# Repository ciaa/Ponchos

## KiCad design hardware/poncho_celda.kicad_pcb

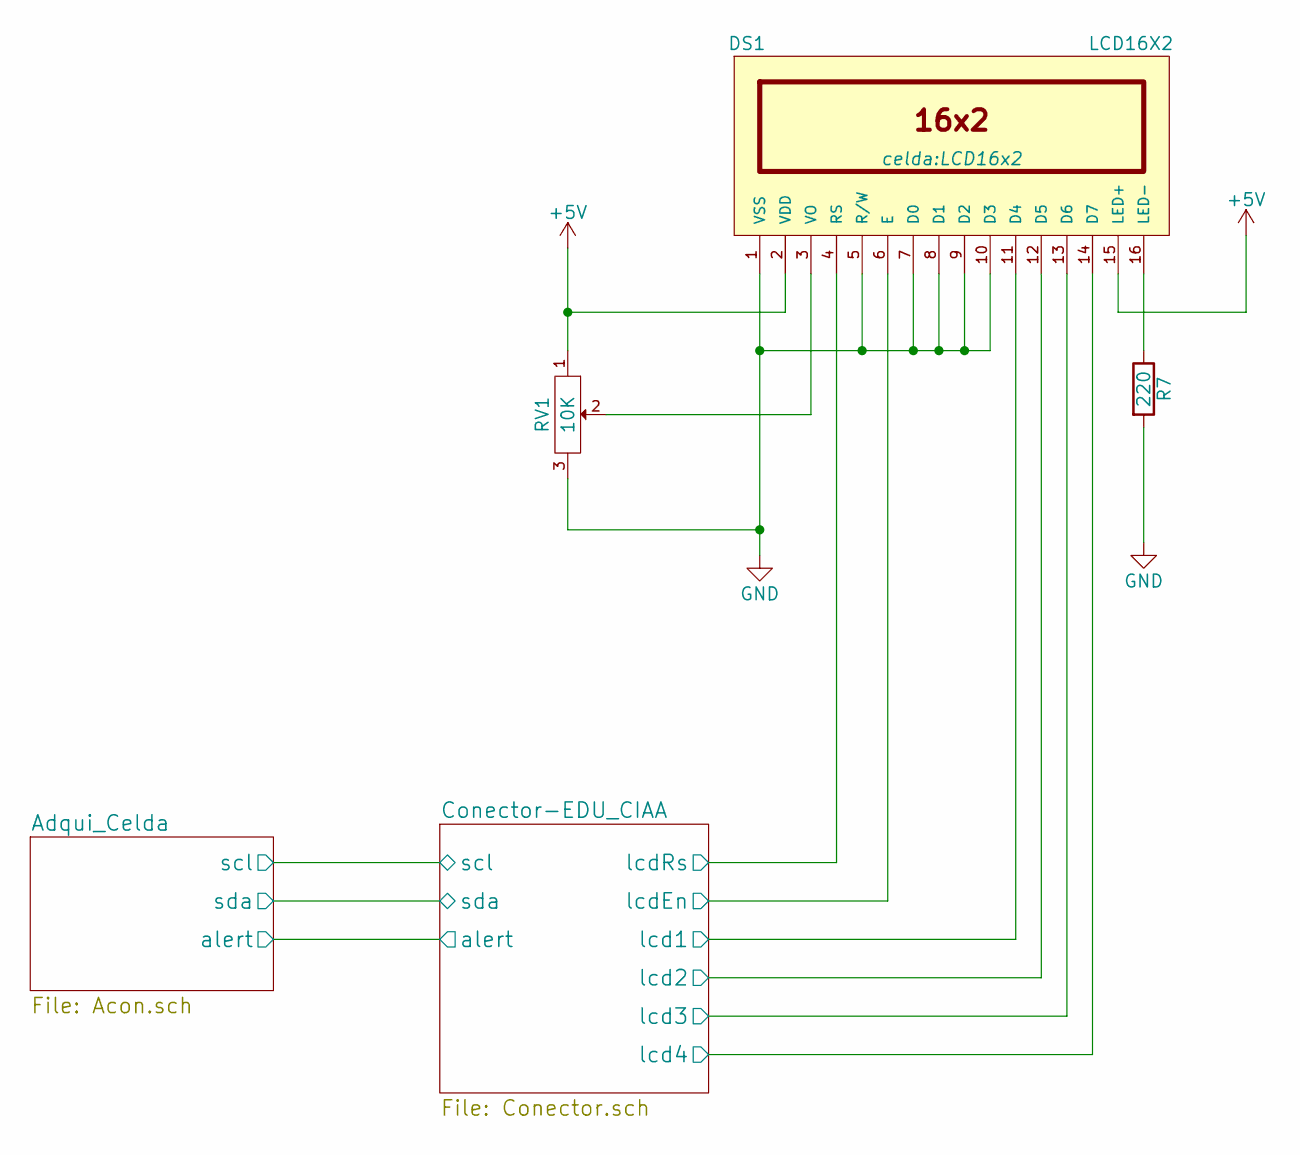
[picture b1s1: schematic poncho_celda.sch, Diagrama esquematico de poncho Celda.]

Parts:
DS1: LCD16X2; LCD16x2
R7: 220; R_1206_HandSoldering
RV1: 10K; POT_SMD

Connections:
+5V: DS1.2 (VDD), DS1.15 (LED+), RV1.1; also elsewhere on the board
/Conector-EDU_CIAA/lcd1: DS1.11 (D4); also elsewhere on the board
/Conector-EDU_CIAA/lcd2: DS1.12 (D5); also elsewhere on the board
/Conector-EDU_CIAA/lcd3: DS1.13 (D6); also elsewhere on the board
/Conector-EDU_CIAA/lcd4: DS1.14 (D7); also elsewhere on the board
/Conector-EDU_CIAA/lcdEn: DS1.6 (E); also elsewhere on the board
/Conector-EDU_CIAA/lcdRs: DS1.4 (RS); also elsewhere on the board
GND: DS1.1 (VSS), DS1.5 (R/W), DS1.7 (D0), DS1.8 (D1), DS1.9 (D2), DS1.10 (D3), R7.2, RV1.3; also elsewhere on the board
unnamed: DS1.3 (VO), RV1.2
unnamed: DS1.16 (LED-), R7.1

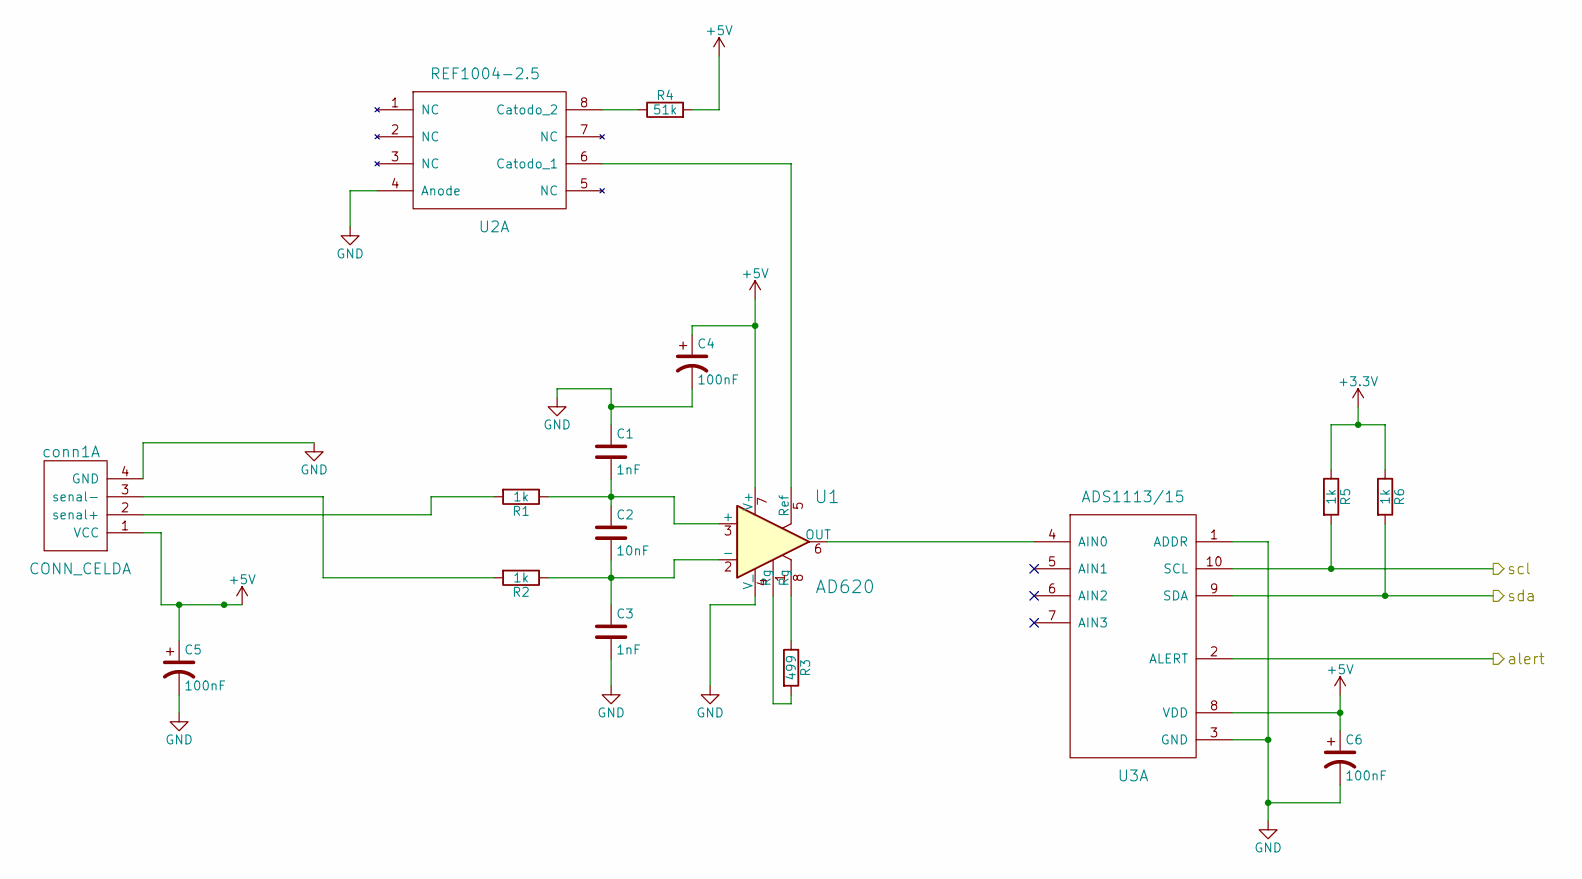
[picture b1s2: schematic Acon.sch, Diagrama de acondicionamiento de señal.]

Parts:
C1, C3: 1nF; C_0603_HandSoldering
C2: 10nF; C_0603_HandSoldering
C4, C5, C6: 100nF; C_0805_HandSoldering
R1, R2, R5, R6: 1k; R_1206_HandSoldering
R3: 499; R_1206_HandSoldering
R4: 51k; R_1206_HandSoldering
U1: AD620; SOIC-8
U2: REF1004-2.5; SOIC-8
U3: ADS1113/15; TSSOP-10_3x3mm_Pitch0.5mm
conn1: CONN_CELDA; bornier4

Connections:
+3V3: R5.1, R6.1; also elsewhere on the board
+5V: C4.1, C5.1, C6.1, R4.2, U1.7 (V+), U3.8 (VDD), conn1.1 (VCC); also elsewhere on the board
/Adqui_Celda/alert: U3.2 (ALERT); also elsewhere on the board
/Adqui_Celda/scl: R5.2, U3.10 (SCL); also elsewhere on the board
/Adqui_Celda/sda: R6.2, U3.9 (SDA); also elsewhere on the board
GND: C1.1, C3.2, C4.2, C5.2, C6.2, U1.4 (V_), U2.4 (Anode), U3.1 (ADDR), U3.3 (GND), conn1.4 (GND); also elsewhere on the board
unnamed: C1.2, C2.1, R1.1, U1.3 (+)
unnamed: C2.2, C3.1, R2.1, U1.2 (-)
unnamed: R1.2, conn1.2 (senal+)
unnamed: R2.2, conn1.3 (senal-)
unnamed: R3.1, U1.8 (Rg)
unnamed: R3.2, U1.1 (Rg)
unnamed: R4.1, U2.8 (Catodo_2)
unnamed: U1.5 (Ref), U2.6 (Catodo_1)
unnamed: U1.6 (OUT), U3.4 (AIN0)

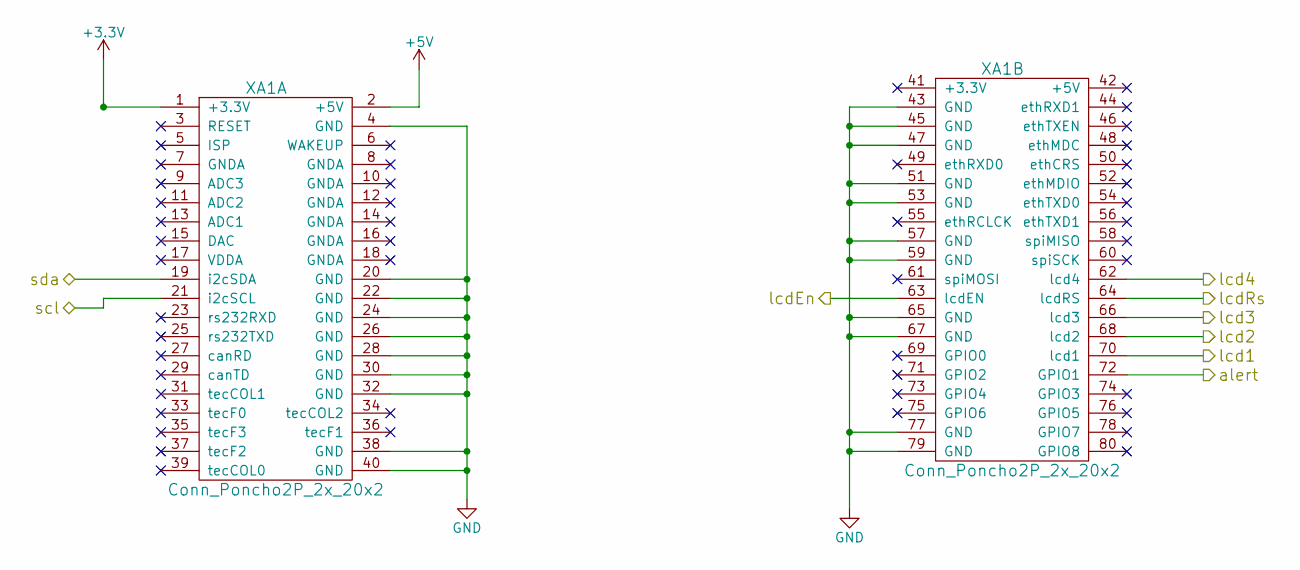
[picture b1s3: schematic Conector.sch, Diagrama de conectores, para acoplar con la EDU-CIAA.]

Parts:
XA1: Conn_Poncho2P_2x_20x2; Conn_Poncho_SinBorde

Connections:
+3V3: XA1.1 (+3.3V); also elsewhere on the board
+5V: XA1.2 (+5V); also elsewhere on the board
/Adqui_Celda/alert: XA1.72 (GPIO1); also elsewhere on the board
/Adqui_Celda/scl: XA1.21 (i2cSCL); also elsewhere on the board
/Adqui_Celda/sda: XA1.19 (i2cSDA); also elsewhere on the board
/Conector-EDU_CIAA/lcd1: XA1.70 (lcd1); also elsewhere on the board
/Conector-EDU_CIAA/lcd2: XA1.68 (lcd2); also elsewhere on the board
/Conector-EDU_CIAA/lcd3: XA1.66 (lcd3); also elsewhere on the board
/Conector-EDU_CIAA/lcd4: XA1.62 (lcd4); also elsewhere on the board
/Conector-EDU_CIAA/lcdEn: XA1.63 (lcdEN); also elsewhere on the board
/Conector-EDU_CIAA/lcdRs: XA1.64 (lcdRS); also elsewhere on the board
GND: XA1.4 (GND), XA1.20 (GND), XA1.22 (GND), XA1.24 (GND), XA1.26 (GND), XA1.28 (GND), XA1.30 (GND), XA1.32 (GND), XA1.38 (GND), XA1.40 (GND), XA1.43 (GND), XA1.45 (GND), XA1.47 (GND), XA1.51 (GND), XA1.53 (GND), XA1.57 (GND), XA1.59 (GND), XA1.65 (GND), XA1.67 (GND), XA1.77 (GND), XA1.79 (GND); also elsewhere on the board

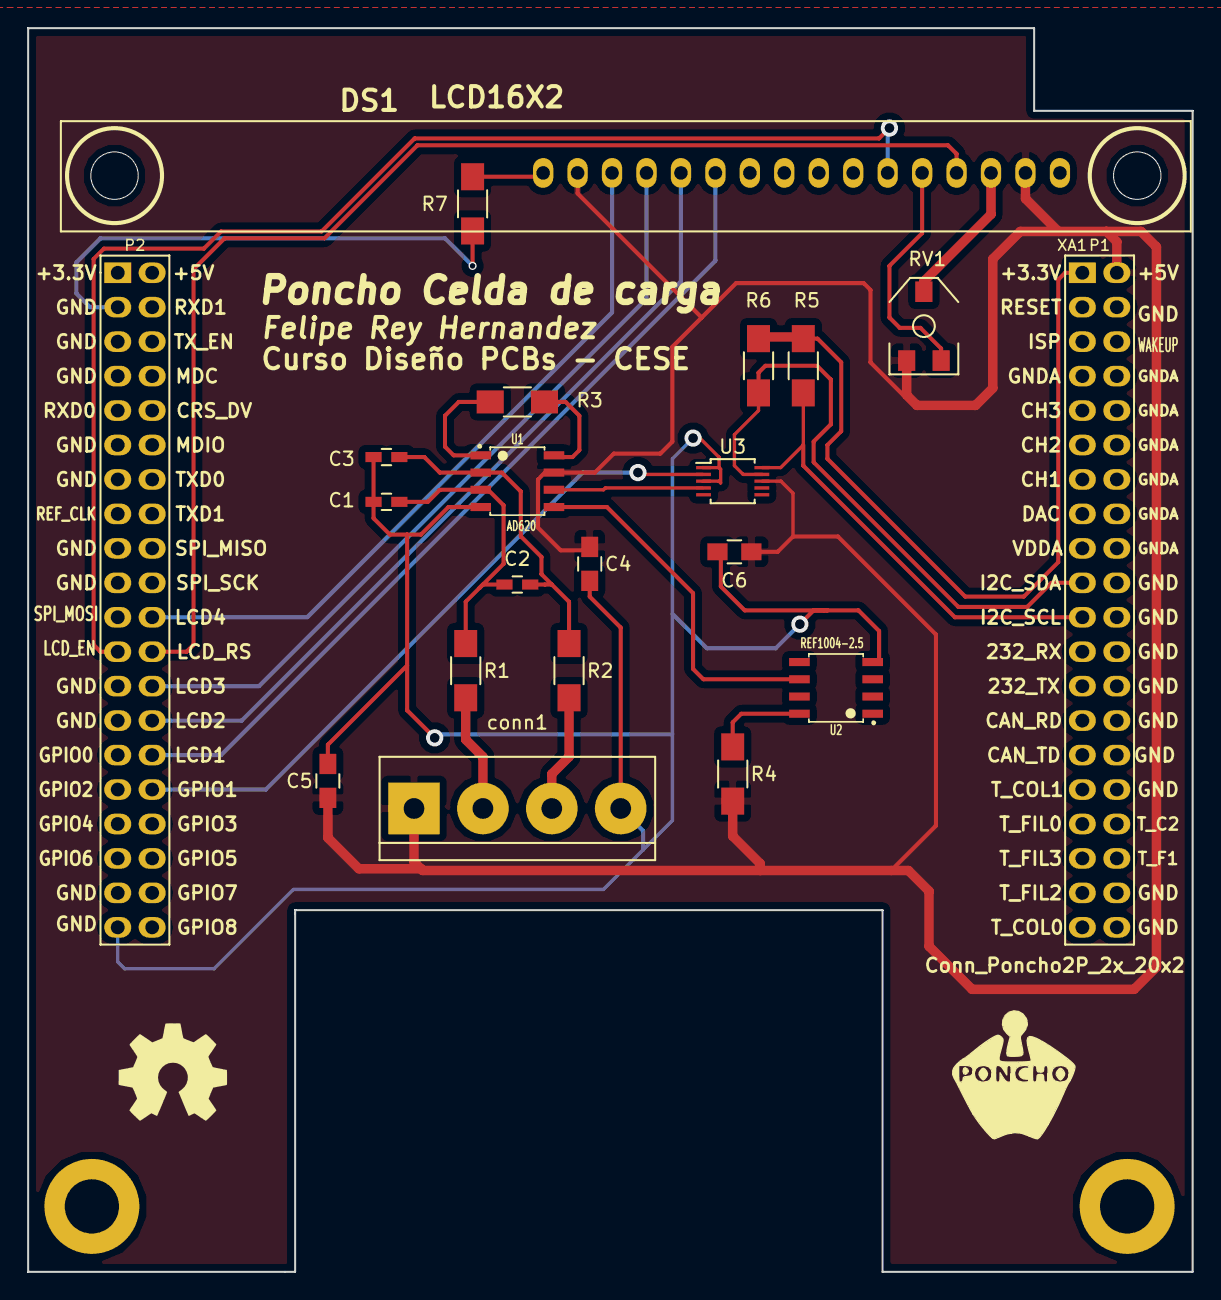
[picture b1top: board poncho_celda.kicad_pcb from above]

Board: 2 copper layers, 85.9 x 91.7 mm, 21 parts (0 on the bottom side), 23 nets.

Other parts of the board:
G101: Logo_OSHWA

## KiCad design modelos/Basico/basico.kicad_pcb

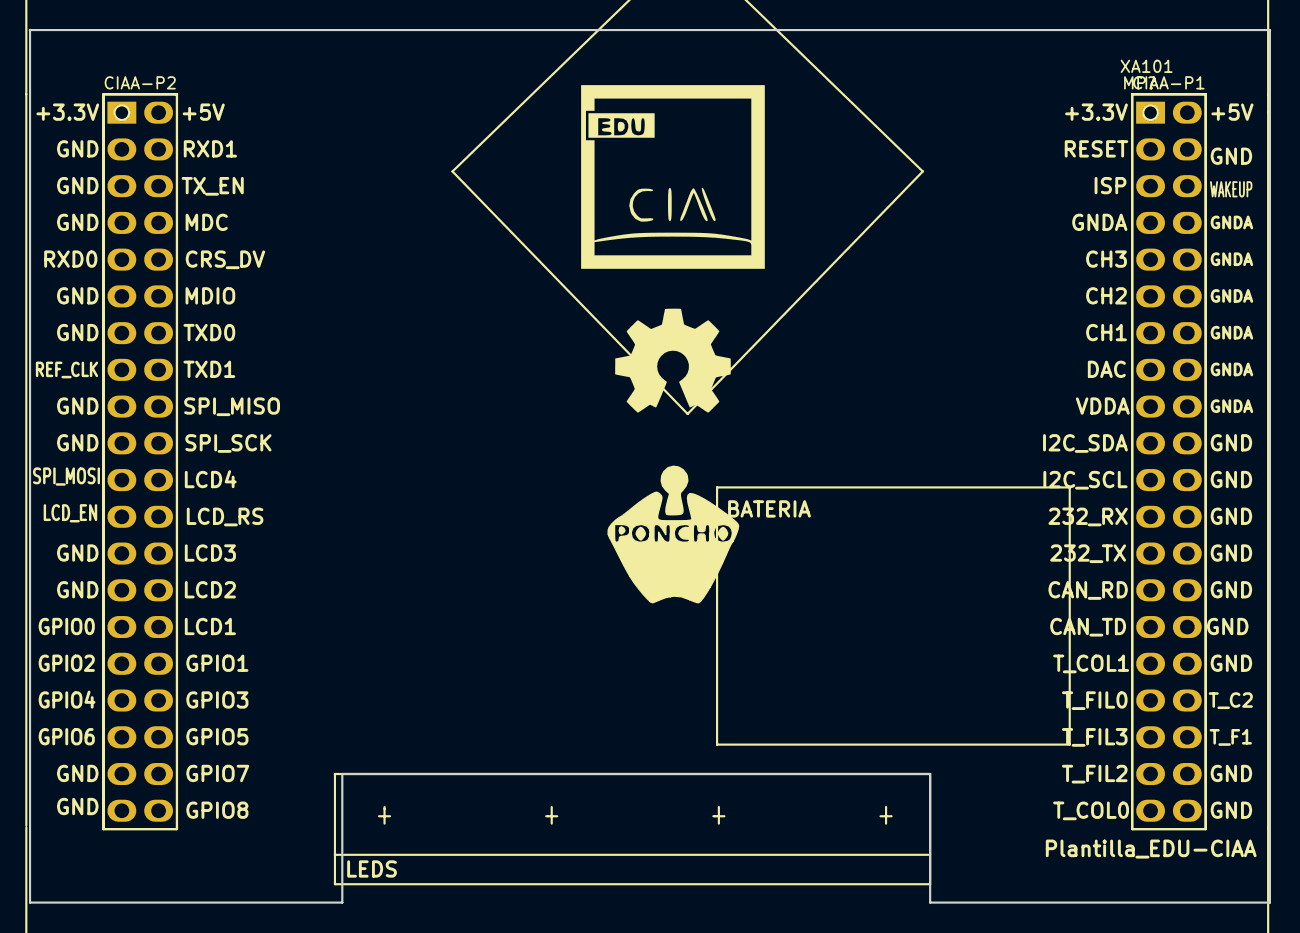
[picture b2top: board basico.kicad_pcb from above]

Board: 2 copper layers, 85.7 x 60.3 mm, 3 parts (0 on the bottom side), 4 nets, no tracks yet.

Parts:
G101: Logo_OSHWA
MP?: Plantilla_EDU-CIAA
XA101: Conn_Poncho2P_2x_20x2; Conn_Poncho_SinBorde

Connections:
+3.3VP: XA101.1, XA101.41
+5V: XA101.2, XA101.42
GND: XA101.4, XA101.20, XA101.22, XA101.24, XA101.26, XA101.28, XA101.30, XA101.32, XA101.38, XA101.40, XA101.43, XA101.45, XA101.47, XA101.51, XA101.53, XA101.57, XA101.59, XA101.65, XA101.67, XA101.77, XA101.79
GNDA: XA101.7, XA101.8, XA101.10, XA101.12, XA101.14, XA101.16, XA101.18

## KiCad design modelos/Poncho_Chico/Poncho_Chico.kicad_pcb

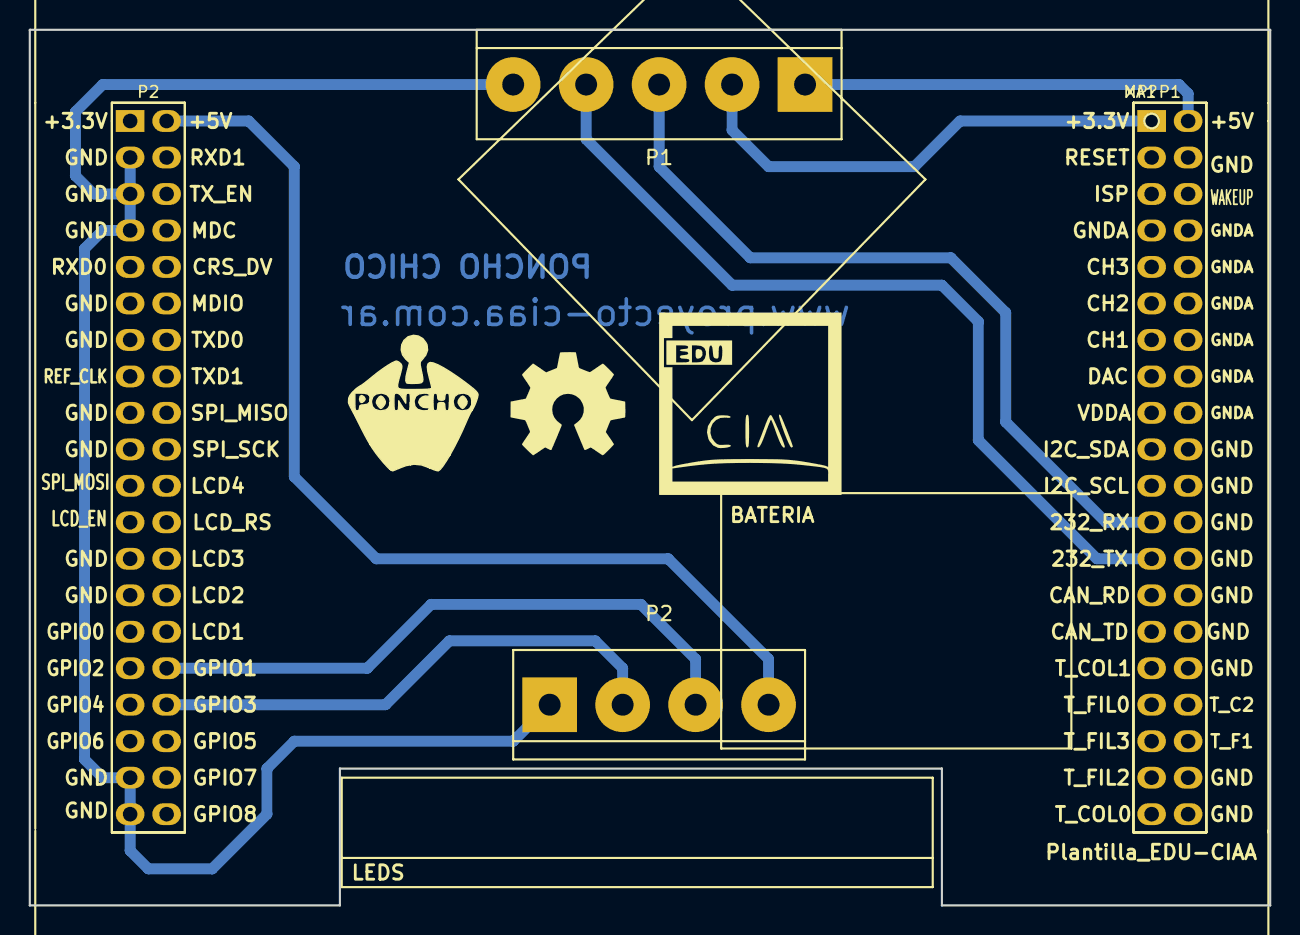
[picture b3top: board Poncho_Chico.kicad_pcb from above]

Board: 2 copper layers, 86.4 x 61.0 mm, 5 parts (0 on the bottom side), 8 nets.

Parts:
G101: Logo_OSHWA
MP?: Plantilla_EDU-CIAA
P1: CONN_5; bornier5
P2: CONN_4; bornier4
XA1: Conn_PonchoMP_2x_20x2; Conn_Poncho_Chico

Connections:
+3.3V: P1.2, XA1.1
+5V: P1.1, XA1.2
+5VP: P2.4, XA1.42
GND: P1.5, P2.1, XA1.43, XA1.45, XA1.47, XA1.77, XA1.79
unnamed: P1.3, XA1.23
unnamed: P1.4, XA1.25
unnamed: P2.2, XA1.74
unnamed: P2.3, XA1.72

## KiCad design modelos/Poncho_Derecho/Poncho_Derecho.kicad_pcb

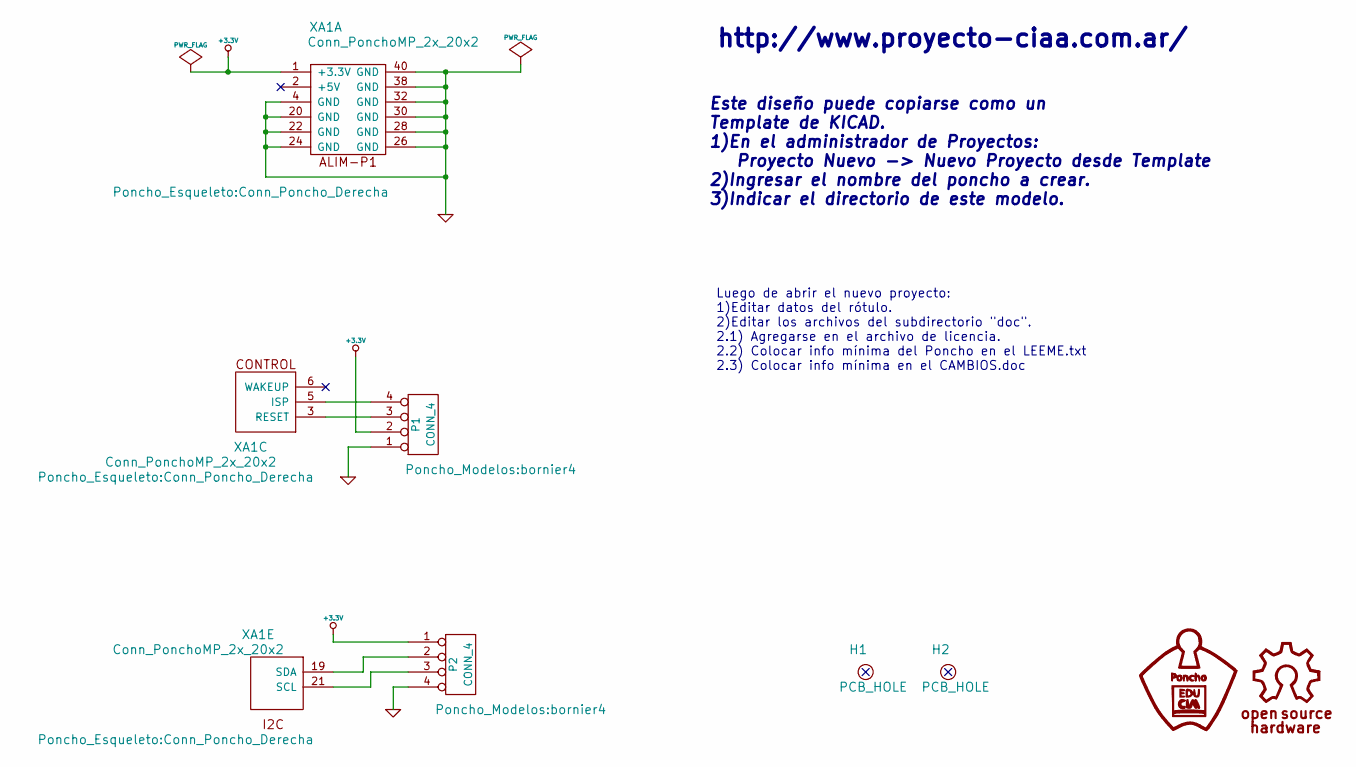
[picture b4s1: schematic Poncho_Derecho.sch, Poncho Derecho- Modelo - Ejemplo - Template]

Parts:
H1, H2: PCB_HOLE; Led_Hole
P1, P2: CONN_4; bornier4
XA1: Conn_PonchoMP_2x_20x2; Conn_Poncho_Derecha

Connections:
+3.3V: P1.2, P2.1, XA1.1 (+3.3V)
GND: P1.1, P2.4, XA1.4 (GND), XA1.20 (GND), XA1.22 (GND), XA1.24 (GND), XA1.26 (GND), XA1.28 (GND), XA1.30 (GND), XA1.32 (GND), XA1.38 (GND), XA1.40 (GND)
unnamed: P1.3, XA1.3 (RESET)
unnamed: P1.4, XA1.5 (ISP)
unnamed: P2.2, XA1.19 (SDA)
unnamed: P2.3, XA1.21 (SCL)

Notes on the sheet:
Este diseño puede copiarse como un Template de KICAD. 1)En el administrador de Proyectos: Proyecto Nuevo -> Nuevo Proyecto desde Template 2)Ingresar el nombre del poncho a crear. 3)Indicar el directorio de este modelo.
http://www.proyecto-ciaa.com.ar/
Luego de abrir el nuevo proyecto: 1)Editar datos del rótulo. 2)Editar los archivos del subdirectorio "doc". 2.1) Agregarse en el archivo de licencia. 2.2) Colocar info mínima del Poncho en el LEEME.txt 2.3) Colocar info mínima en el CAMBIOS.doc

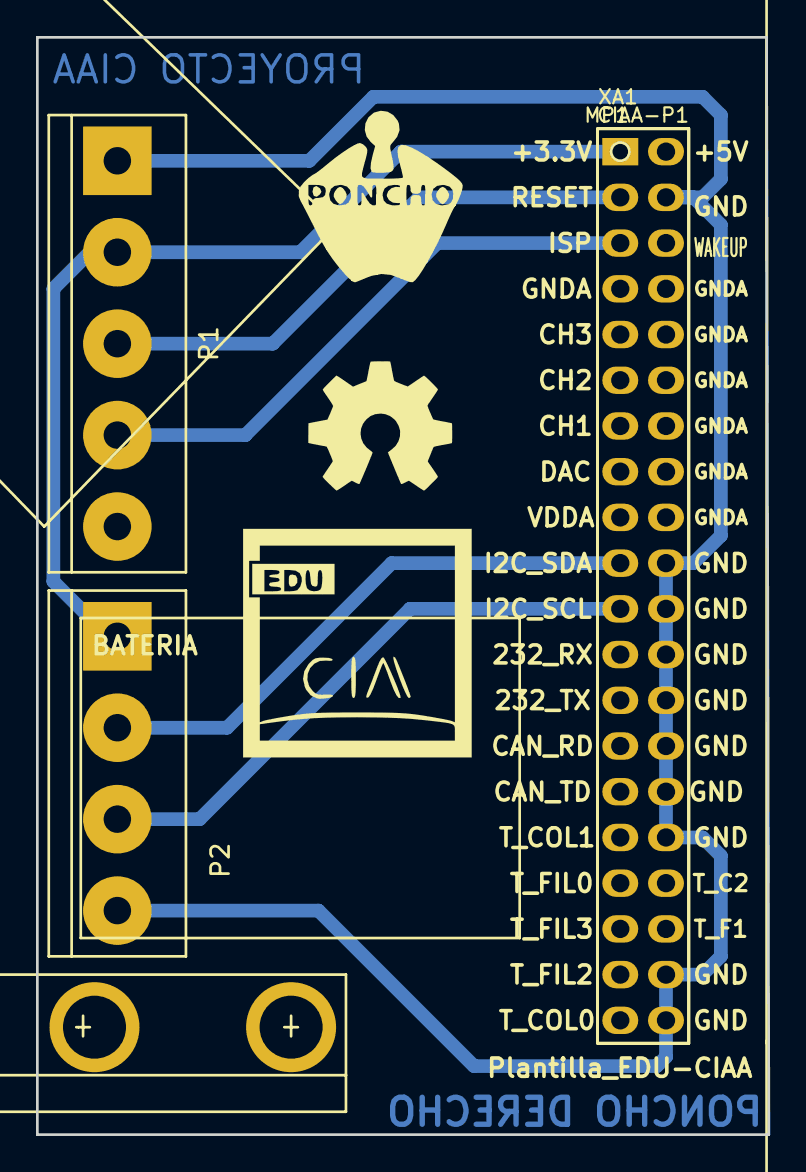
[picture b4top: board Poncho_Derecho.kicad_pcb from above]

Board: 2 copper layers, 40.6 x 61.0 mm, 7 parts (0 on the bottom side), 6 nets.

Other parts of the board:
G101: Logo_OSHWA
MP1: Plantilla_EDU-CIAA

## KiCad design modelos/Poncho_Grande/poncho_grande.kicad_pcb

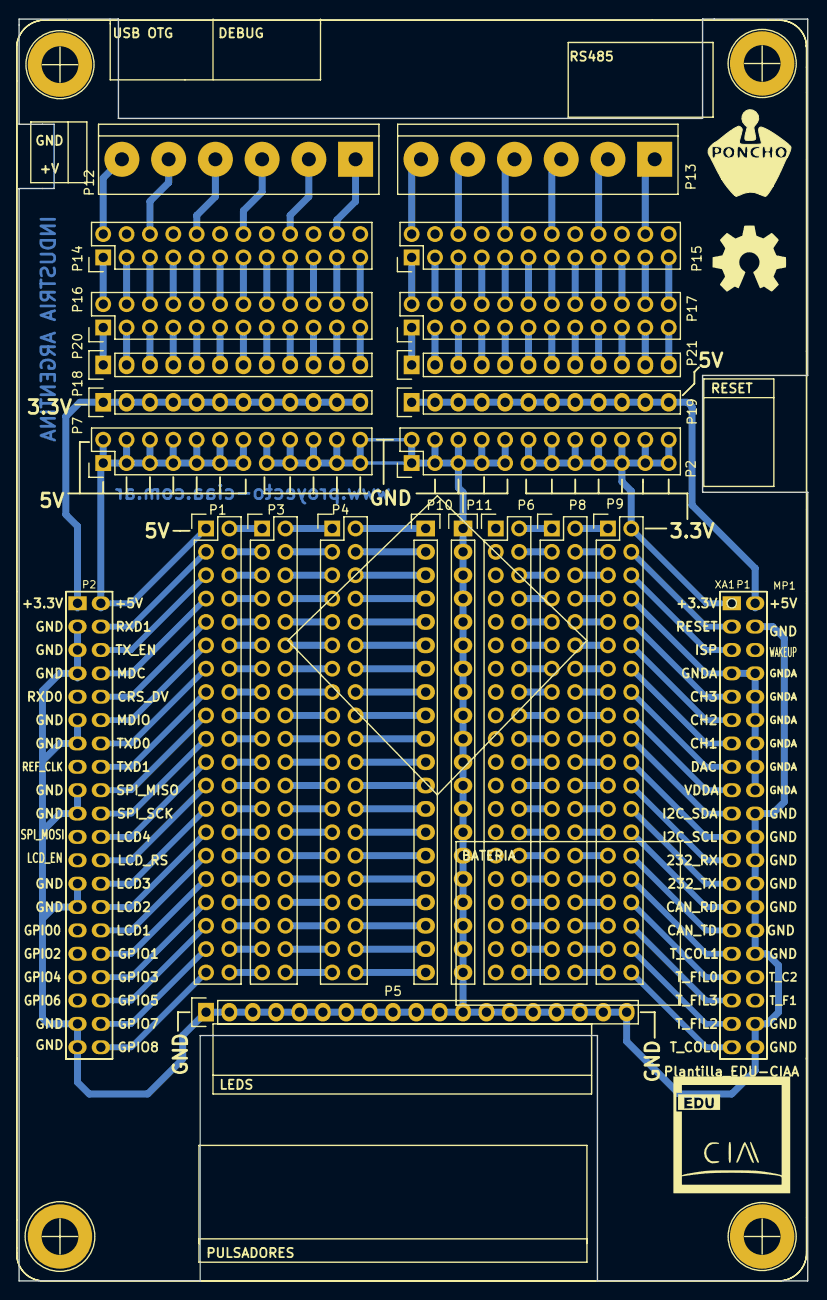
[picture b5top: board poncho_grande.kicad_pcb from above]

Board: 2 copper layers, 85.7 x 137.2 mm, 24 parts (0 on the bottom side), 203 nets.

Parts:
G101: Logo_OSHWA
MP1: Plantilla_EDU-CIAA
P1, P3, P4, P6, P8, P9: CONN_02X20; Pin_Header_Straight_2x20
P2, P7: CONN_01X20; Pin_Header_Straight_2x12
P5: CONN_01X19; Pin_Header_Straight_1x19
P10, P11: CONN_01X20; Pin_Header_Straight_1x20
P12, P13: CONN_01X06; bornier6
P14, P15, P16, P17: CONN_02X12; Pin_Header_Straight_2x12
P18, P19, P20, P21: CONN_01X12; Pin_Header_Straight_1x12
XA1: poncho_grande

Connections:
+3.3V: P2.11, P2.12, P2.13, P2.14, P2.15, P2.16, P2.17, P2.18, P2.19, P2.20, P2.21, P2.22, P2.23, P2.24, P9.2, XA1.1
+3.3VADC: P9.18, XA1.17
+3.3VP: P18.1, P18.2, P18.3, P18.4, P18.5, P18.6, P18.7, P18.8, P18.9, P18.10, P18.11, P18.12, XA1.41
+5V: P19.1, P19.2, P19.3, P19.4, P19.5, P19.6, P19.7, P19.8, P19.9, P19.10, P19.11, P19.12, XA1.2
+5VP: P1.1, P7.1, P7.2, P7.3, P7.4, P7.5, P7.6, P7.7, P7.8, P7.9, P7.10, P7.11, P7.12, P7.13, P7.14, XA1.42
/Circuito Principal/ADC1: P9.14, XA1.13
/Circuito Principal/ADC2: P9.12, XA1.11
/Circuito Principal/ADC3: P9.10, XA1.9
/Circuito Principal/COL0: P9.40, XA1.39
/Circuito Principal/COL1: P9.32, XA1.31
/Circuito Principal/CRS: P1.9, XA1.50
/Circuito Principal/DAC: P9.16, XA1.15
/Circuito Principal/F0: P9.34, XA1.33
/Circuito Principal/F2: P9.38, XA1.37
/Circuito Principal/F3: P9.36, XA1.35
/Circuito Principal/GPIO1: P1.31, XA1.72
/Circuito Principal/GPIO3: P1.33, XA1.74
/Circuito Principal/GPIO5: P1.35, XA1.76
/Circuito Principal/GPIO7: P1.37, XA1.78
/Circuito Principal/GPIO8: P1.39, XA1.80
/Circuito Principal/ISP: P9.6, XA1.5
/Circuito Principal/LCD1: P1.29, XA1.70
/Circuito Principal/LCD2: P1.27, XA1.68
/Circuito Principal/LCD3: P1.25, XA1.66
/Circuito Principal/LCD4: P1.21, XA1.62
/Circuito Principal/MDC: P1.7, XA1.48
/Circuito Principal/MDIO: P1.11, XA1.52
/Circuito Principal/MISO: P1.17, XA1.58
/Circuito Principal/RD: P9.28, XA1.27
/Circuito Principal/RESET: P9.4, XA1.3
/Circuito Principal/RS: P1.23, XA1.64
/Circuito Principal/RXD: P9.24, XA1.23
/Circuito Principal/RXD1: P1.3, XA1.44
/Circuito Principal/SCL: P9.22, XA1.21
/Circuito Principal/SDA: P9.20, XA1.19
/Circuito Principal/TD: P9.30, XA1.29
/Circuito Principal/TXD: P9.26, XA1.25
/Circuito Principal/TXD0: P1.13, XA1.54
/Circuito Principal/TXD1: P1.15, XA1.56
/Circuito Principal/TXEN: P1.5, XA1.46
/Circuito Principal/spiCCK: P1.19, XA1.60
GND: P2.1, P2.2, P2.3, P2.4, P2.5, P2.6, P2.7, P2.8, P2.9, P2.10, P5.1, P5.2, P5.3, P5.4, P5.5, P5.6, P5.7, P5.8, P5.9, P5.10, P5.11, P5.12, P5.13, P5.14, P5.15, P5.16, P5.17, P5.18, P5.19, P7.15, P7.16, P7.17, P7.18, P7.19, P7.20, P7.21, P7.22, P7.23, P7.24, P11.1, P11.2, P11.3, P11.4, P11.5, P11.6, P11.7, P11.8, P11.9, P11.10, P11.11, P11.12, P11.13, P11.14, P11.15, P11.16, P11.17, P11.18, P11.19, P11.20, XA1.4, XA1.20, XA1.22, XA1.24, XA1.26, XA1.28, XA1.30, XA1.32, XA1.38, XA1.40, XA1.43, XA1.45, XA1.47, XA1.51, XA1.53, XA1.57, XA1.59, XA1.65, XA1.67, XA1.77, XA1.79
GNDA: P9.8, XA1.7, XA1.8, XA1.10, XA1.12, XA1.14, XA1.16, XA1.18
unnamed: P1.2, P3.1
unnamed: P1.4, P3.3
unnamed: P1.6, P3.5
unnamed: P1.8, P3.7
unnamed: P1.10, P3.9
unnamed: P1.12, P3.11
unnamed: P1.14, P3.13
unnamed: P1.16, P3.15
unnamed: P1.18, P3.17
unnamed: P1.20, P3.19
unnamed: P1.22, P3.21
unnamed: P1.24, P3.23
unnamed: P1.26, P3.25
unnamed: P1.28, P3.27
unnamed: P1.30, P3.29
unnamed: P1.32, P3.31
unnamed: P1.34, P3.33
unnamed: P1.36, P3.35
unnamed: P1.38, P3.37
unnamed: P1.40, P3.39
unnamed: P3.2, P4.1
unnamed: P3.4, P4.3
unnamed: P3.6, P4.5
unnamed: P3.8, P4.7
unnamed: P3.10, P4.9
unnamed: P3.12, P4.11
unnamed: P3.14, P4.13
unnamed: P3.16, P4.15
unnamed: P3.18, P4.17
unnamed: P3.20, P4.19
unnamed: P3.22, P4.21
unnamed: P3.24, P4.23
unnamed: P3.26, P4.25
unnamed: P3.28, P4.27
unnamed: P3.30, P4.29
unnamed: P3.32, P4.31
unnamed: P3.34, P4.33
unnamed: P3.36, P4.35
unnamed: P3.38, P4.37
unnamed: P3.40, P4.39
unnamed: P6.2, P8.1
unnamed: P6.4, P8.3
unnamed: P6.6, P8.5
unnamed: P6.8, P8.7
unnamed: P6.10, P8.9
unnamed: P6.12, P8.11
unnamed: P6.14, P8.13
unnamed: P6.16, P8.15
unnamed: P6.18, P8.17
unnamed: P6.20, P8.19
unnamed: P6.22, P8.21
unnamed: P6.24, P8.23
unnamed: P6.26, P8.25
unnamed: P6.28, P8.27
unnamed: P6.30, P8.29
unnamed: P6.32, P8.31
unnamed: P6.34, P8.33
unnamed: P6.36, P8.35
unnamed: P6.38, P8.37
unnamed: P6.40, P8.39
unnamed: P8.2, P9.1
unnamed: P8.4, P9.3
unnamed: P8.6, P9.5
unnamed: P8.8, P9.7
unnamed: P8.10, P9.9
unnamed: P8.12, P9.11
unnamed: P8.14, P9.13
unnamed: P8.16, P9.15
unnamed: P8.18, P9.17
unnamed: P8.20, P9.19
unnamed: P8.22, P9.21
unnamed: P8.24, P9.23
unnamed: P8.26, P9.25
unnamed: P8.28, P9.27
unnamed: P8.30, P9.29
unnamed: P8.32, P9.31
unnamed: P8.34, P9.33
unnamed: P8.36, P9.35
unnamed: P8.38, P9.37
unnamed: P8.40, P9.39
unnamed: P4.2, P10.1
unnamed: P4.4, P10.2
unnamed: P4.6, P10.3
unnamed: P4.8, P10.4
unnamed: P4.10, P10.5
unnamed: P4.12, P10.6
unnamed: P4.14, P10.7
unnamed: P4.16, P10.8
unnamed: P4.18, P10.9
unnamed: P4.20, P10.10
unnamed: P4.22, P10.11
unnamed: P4.24, P10.12
unnamed: P4.26, P10.13
unnamed: P4.28, P10.14
unnamed: P4.30, P10.15
unnamed: P4.32, P10.16
unnamed: P4.34, P10.17
unnamed: P4.36, P10.18
unnamed: P4.38, P10.19
unnamed: P4.40, P10.20
unnamed: P12.1, P14.22
unnamed: P12.2, P14.18
unnamed: P12.3, P14.14
unnamed: P12.4, P14.10
unnamed: P12.5, P14.6
unnamed: P12.6, P14.2
unnamed: P13.1, P15.22
unnamed: P13.2, P15.18
unnamed: P13.3, P15.14
unnamed: P13.4, P15.10
unnamed: P13.5, P15.6
unnamed: P13.6, P15.2
unnamed: P14.1, P16.2
unnamed: P14.3, P16.4
unnamed: P14.5, P16.6
unnamed: P14.7, P16.8
unnamed: P14.9, P16.10
unnamed: P14.11, P16.12
unnamed: P14.13, P16.14
unnamed: P14.15, P16.16
unnamed: P14.17, P16.18
unnamed: P14.19, P16.20
unnamed: P14.21, P16.22
unnamed: P14.23, P16.24
unnamed: P15.1, P17.2
unnamed: P15.3, P17.4
unnamed: P15.5, P17.6
unnamed: P15.7, P17.8
unnamed: P15.9, P17.10
unnamed: P15.11, P17.12
unnamed: P15.13, P17.14
unnamed: P15.15, P17.16
unnamed: P15.17, P17.18
unnamed: P15.19, P17.20
unnamed: P15.21, P17.22
unnamed: P15.23, P17.24
unnamed: P16.1, P20.1
unnamed: P16.3, P20.2
unnamed: P16.5, P20.3
unnamed: P16.7, P20.4
unnamed: P16.9, P20.5
unnamed: P16.11, P20.6
unnamed: P16.13, P20.7
unnamed: P16.15, P20.8
unnamed: P16.17, P20.9
unnamed: P16.19, P20.10
unnamed: P16.21, P20.11
unnamed: P16.23, P20.12
unnamed: P17.1, P21.1
unnamed: P17.3, P21.2
unnamed: P17.5, P21.3
unnamed: P17.7, P21.4
unnamed: P17.9, P21.5
unnamed: P17.11, P21.6
unnamed: P17.13, P21.7
unnamed: P17.15, P21.8
unnamed: P17.17, P21.9
unnamed: P17.19, P21.10
unnamed: P17.21, P21.11
unnamed: P17.23, P21.12

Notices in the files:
hardware/Acon.sch:
Licencia GPL V3
